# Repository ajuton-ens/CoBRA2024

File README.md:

# CoBRA

Le projet CoBRA (Course de Ballons Réactifs et Autonomes) à pour objectif de construire un ballon dirigeable capable de suivre un parcours de façon autonome et de larguer un colis

## 1 Constitution des équipes

Chaque équipe doit fournir au moins 1 membre à chacun des 4 groupes de travail suivants :
* Préhension & Dépot
* Optimisation de la cinématique de vol
* Modélisation & Contrôle/Commande
* Informatique embarquée & Localisation

## 2 Analyse fonctionnelle et état de l'art
La première séance est consacrée à un travail d'étude générale du problème et d'état de l'art (projet 2023_2024 et autres dirigeables blimp).
* Découper le problème en plusieurs fonctions,
* Pour chaque fonction, spécifier les performances attendues,
* Etudier les solutions retenues en 2023 et les solutions retenues pour d'autres dirigeables,
* Etablir un schéma synoptique du dirigeable.

La semaine suivante, les groupes de travail commenceront leurs études.

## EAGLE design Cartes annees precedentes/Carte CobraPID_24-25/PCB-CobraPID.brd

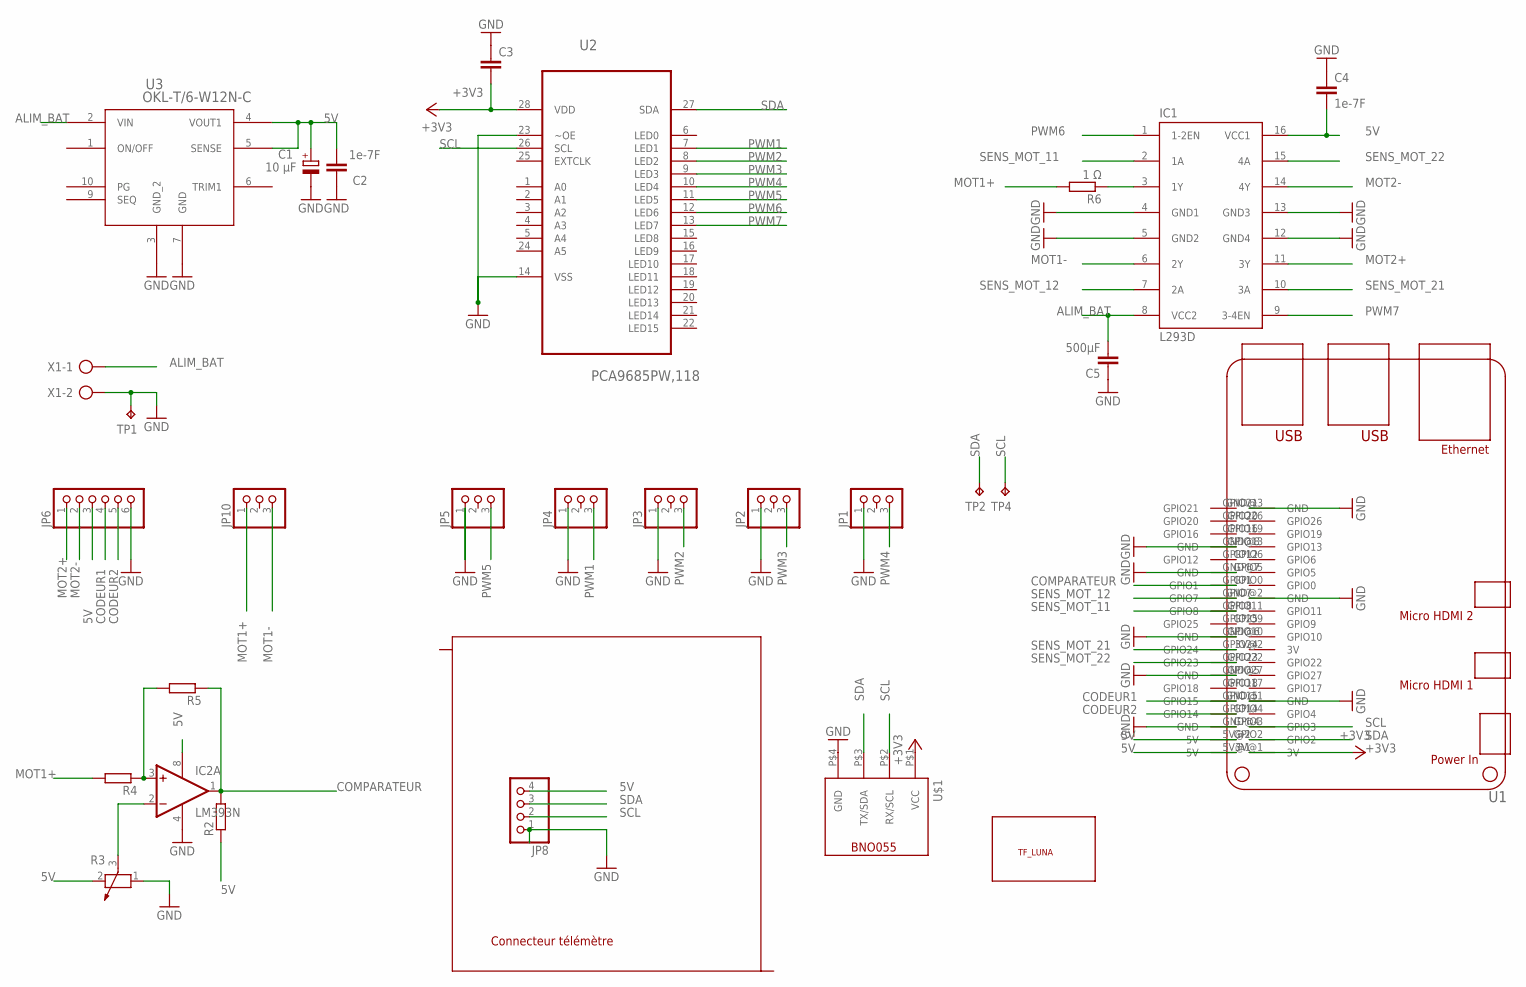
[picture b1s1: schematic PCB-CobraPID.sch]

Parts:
C1: 10 μF; E5-10,5
C2, C4: 1e-7F; C1206
C3: C-EUC1206; C1206
C5: 500μF; C1206
IC1: L293D; DIL16
IC2: LM393N; DIL08
JP1, JP2, JP3, JP4, JP5, JP10: PINHD-1X3/90; 1X03/90
JP6: PINHD-1X6/90; 1X06/90
JP8: PINHD-1X4; 1X04
R2, R4, R5: R-EU_R1206; R1206
R3: POTENTIOMETER_PT-10; PT-10
R6: 1 Ω; R1206
TP1, TP2, TP4: TPPAD1-17; P1-17
U1: RPI5
U2: PCA9685PW,118; SOP65P640X110-28N
U3: OKL-T/6-W12N-C; OKL-T/6-W12N-C_MUR
U$1: MODULE_BNO055
U$2: TF_LUNA
X1: AK500/2

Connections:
5V: C1.+, C2.2, C4.2, IC1.16 (VCC1), IC2.8 (V+), JP6.3, JP8.4, R2.1, R3.2, U1.5V@1 (5V), U1.5V@2 (5V), U3.4 (VOUT1), U3.5 (SENSE)
+3V3: C3.2, U1.3V@1 (3V), U2.28 (VDD), U$1.P$1 (VCC)
ALIM_BAT: C5.2, IC1.8 (VCC2), U3.2 (VIN), X1.1
CODEUR1: JP6.4, U1.GPIO15
CODEUR2: JP6.5, U1.GPIO14
COMPARATEUR: IC2.1 (OUT), R2.2, R5.1, U1.GPIO1
GND: C1.-, C2.1, C3.1, C4.1, C5.1, IC1.4 (GND1), IC1.5 (GND2), IC1.12 (GND4), IC1.13 (GND3), IC2.4 (V-), JP1.1, JP2.1, JP3.1, JP4.1, JP6.6, JP8.1, R3.1, TP1.TP, U1.GND@1 (GND), U1.GND@2 (GND), U1.GND@3 (GND), U1.GND@4 (GND), U1.GND@5 (GND), U1.GND@6 (GND), U1.GND@7 (GND), U1.GND@8 (GND), U2.14 (VSS), U2.23 (~OE), U3.3 (GND_2), U3.7 (GND), U$1.P$4 (GND), X1.2
GND1: JP5.1
MOT1+: JP10.1, R4.2, R6.2
MOT1-: IC1.6 (2Y), JP10.3
MOT2+: IC1.11 (3Y), JP6.1
MOT2-: IC1.14 (4Y), JP6.2
unnamed: IC2.3 (+IN), R4.1, R5.2
unnamed: IC2.2 (-IN), R3.3
unnamed: IC1.3 (1Y), R6.1
PWM1: JP4.3, U2.7 (LED1)
PWM2: JP3.3, U2.8 (LED2)
PWM3: JP2.3, U2.9 (LED3)
PWM4: JP1.3, U2.10 (LED4)
PWM5: JP5.3, U2.11 (LED5)
PWM6: IC1.1 (1-2EN), U2.12 (LED6)
PWM7: IC1.9 (3-4EN), U2.13 (LED7)
SCL: JP8.2, TP4.TP, U1.GPIO3, U2.26 (SCL), U$1.P$2 (RX/SCL)
SDA: JP8.3, TP2.TP, U1.GPIO2, U2.27 (SDA), U$1.P$3 (TX/SDA)
SENS_MOT_11: IC1.2 (1A), U1.GPIO8
SENS_MOT_12: IC1.7 (2A), U1.GPIO7
SENS_MOT_21: IC1.10 (3A), U1.GPIO24
SENS_MOT_22: IC1.15 (4A), U1.GPIO23

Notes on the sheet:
Connecteur télémètre

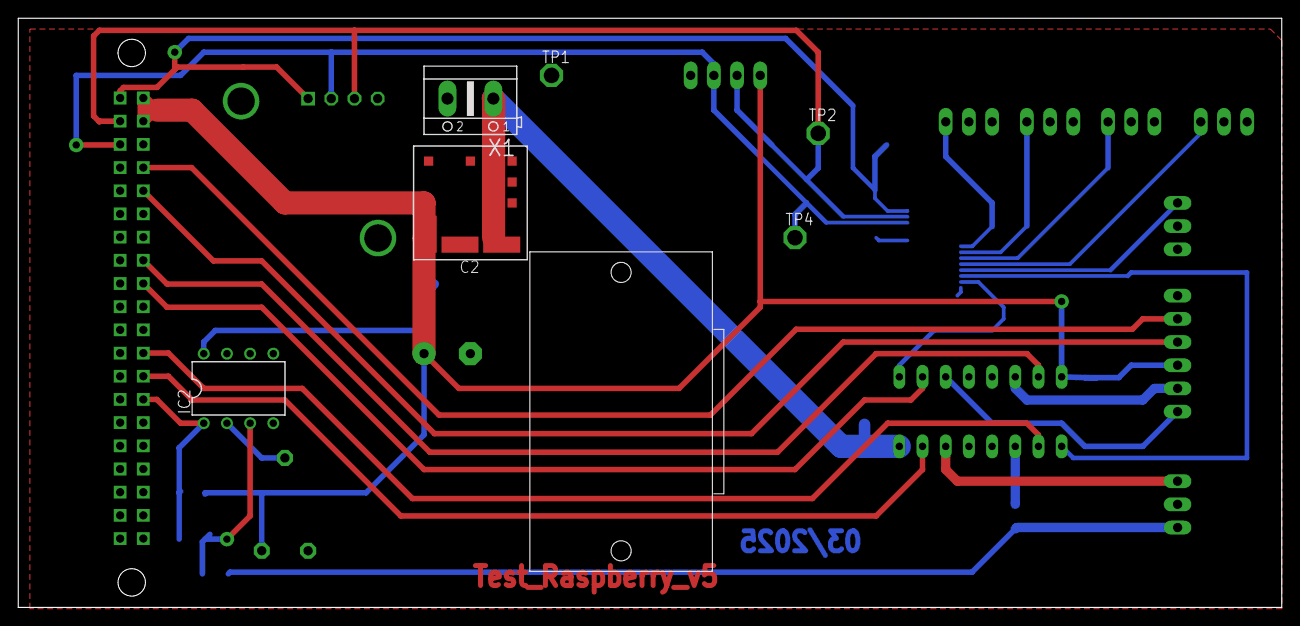
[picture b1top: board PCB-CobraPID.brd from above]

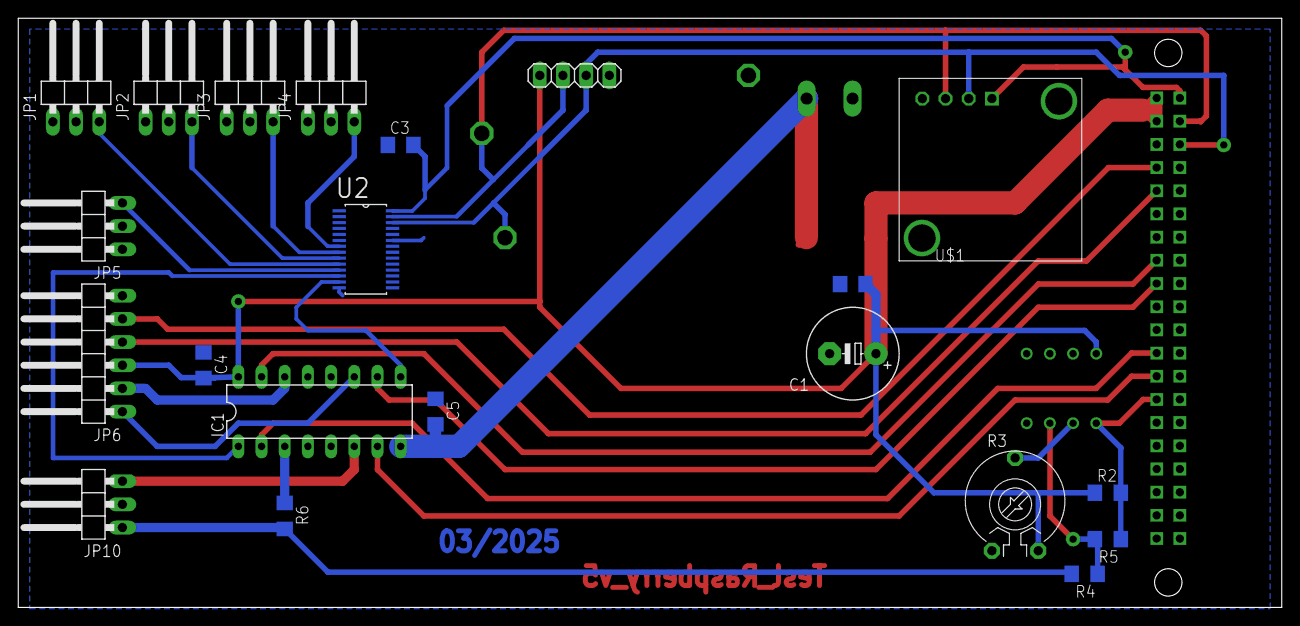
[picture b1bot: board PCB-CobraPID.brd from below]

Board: 2 copper layers, 138.4 x 64.5 mm, 29 parts (21 on the bottom side), 27 nets.

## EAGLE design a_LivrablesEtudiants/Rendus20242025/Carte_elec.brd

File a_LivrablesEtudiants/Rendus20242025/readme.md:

# Info 2024/25

Pour désactiver la sortie 5 volts de la carte Raspberry pi 5

Ouvrir le fichier config.txt: sudo nano /boot/firmware/config.txt

Ajouter la igne suivante :
PSU_MAX_CURRENT=5000

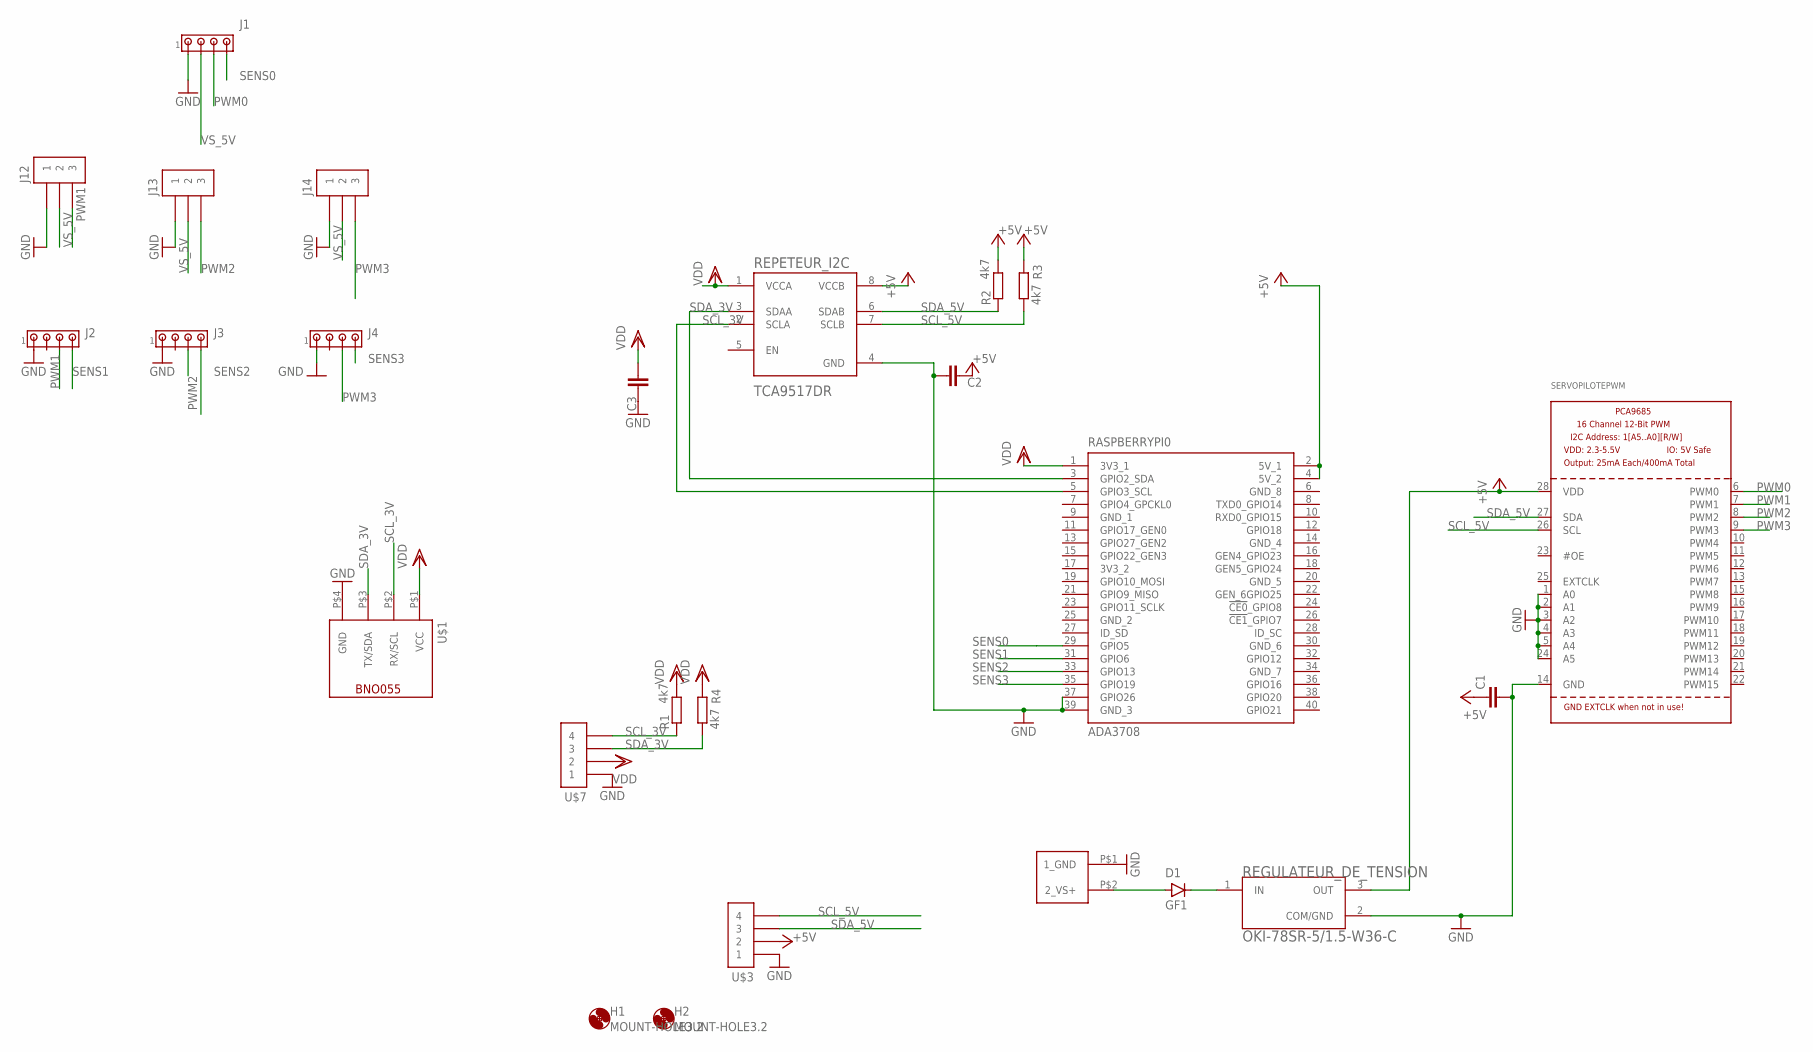
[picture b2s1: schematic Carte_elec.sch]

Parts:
C1, C2, C3: C-EUC1206; C1206
D1: GF1; SMA-DO214AC
H1, H2: MOUNT-HOLE3.2; 3,2
J1, J2, J3, J4: MTA04-100; 10X04MTA
J12, J13, J14: CAVALIER_3
R1, R2, R3, R4: 4k7; R1206
RASPBERRYPI0: ADA3708; MODULE_ADA3708
REGULATEUR_DE_TENSION: OKI-78SR-5/1.5-W36-C; CONV_OKI-78SR-5/1.5-W36-C
REPETEUR_I2C: TCA9517DR; SOIC127P599X175-8N
SERVOPILOTEPWM: PCA9685; TSSOP28
U$1: MODULE_BNO055
U$2: CONN_ALIM
U$3, U$7: MOLEX_4_DROIT

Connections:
3V3_2: RASPBERRYPI0.17 (3V3_2)
+5V: C1.1, C2.1, R2.2, R3.2, RASPBERRYPI0.2 (5V_1), RASPBERRYPI0.4 (5V_2), REGULATEUR_DE_TENSION.3 (OUT), REPETEUR_I2C.8 (VCCB), SERVOPILOTEPWM.28 (VDD), U$3.P$2 (2)
GND: C1.2, C2.2, C3.1, J1.1, J2.1, J3.1, J4.1, J12.P$1 (1), J13.P$1 (1), J14.P$1 (1), RASPBERRYPI0.37 (GPIO26), RASPBERRYPI0.39 (GND_3), REGULATEUR_DE_TENSION.2 (COM/GND), REPETEUR_I2C.4 (GND), SERVOPILOTEPWM.1 (A0), SERVOPILOTEPWM.2 (A1), SERVOPILOTEPWM.3 (A2), SERVOPILOTEPWM.4 (A3), SERVOPILOTEPWM.5 (A4), SERVOPILOTEPWM.14 (GND), SERVOPILOTEPWM.24 (A5), U$1.P$4 (GND), U$2.P$1 (1_GND), U$3.P$1 (1), U$7.P$1 (1)
GND_1: RASPBERRYPI0.9 (GND_1)
GND_2: RASPBERRYPI0.25 (GND_2)
GND_4: RASPBERRYPI0.14 (GND_4)
GND_5: RASPBERRYPI0.20 (GND_5)
GND_6: RASPBERRYPI0.30 (GND_6)
GND_7: RASPBERRYPI0.34 (GND_7)
GND_8: RASPBERRYPI0.6 (GND_8)
unnamed: D1.A, U$2.P$2 (2_VS+)
unnamed: D1.K (C), REGULATEUR_DE_TENSION.1 (IN)
PWM0: J1.3, SERVOPILOTEPWM.6 (PWM0)
PWM1: J2.3, J12.P$3 (3), SERVOPILOTEPWM.7 (PWM1)
PWM2: J3.3, J13.P$3 (3), SERVOPILOTEPWM.8 (PWM2)
PWM3: J4.3, J14.P$3 (3), SERVOPILOTEPWM.9 (PWM3)
SCL_3V: R1.1, RASPBERRYPI0.5 (GPIO3_SCL), REPETEUR_I2C.2 (SCLA), U$1.P$2 (RX/SCL), U$7.P$4 (4)
SCL_5V: R3.1, REPETEUR_I2C.7 (SCLB), SERVOPILOTEPWM.26 (SCL), U$3.P$4 (4)
SDA_3V: R4.1, RASPBERRYPI0.3 (GPIO2_SDA), REPETEUR_I2C.3 (SDAA), U$1.P$3 (TX/SDA), U$7.P$3 (3)
SDA_5V: R2.1, REPETEUR_I2C.6 (SDAB), SERVOPILOTEPWM.27 (SDA), U$3.P$3 (3)
SENS0: J1.4, RASPBERRYPI0.29 (GPIO5)
SENS1: J2.4, RASPBERRYPI0.31 (GPIO6)
SENS2: J3.4, RASPBERRYPI0.33 (GPIO13)
SENS3: J4.4, RASPBERRYPI0.35 (GPIO19)
VDD: C3.2, R1.2, R4.2, RASPBERRYPI0.1 (3V3_1), REPETEUR_I2C.1 (VCCA), U$1.P$1 (VCC), U$7.P$2 (2)
VS_5V: J1.2, J12.P$2 (2), J14.P$2 (2)

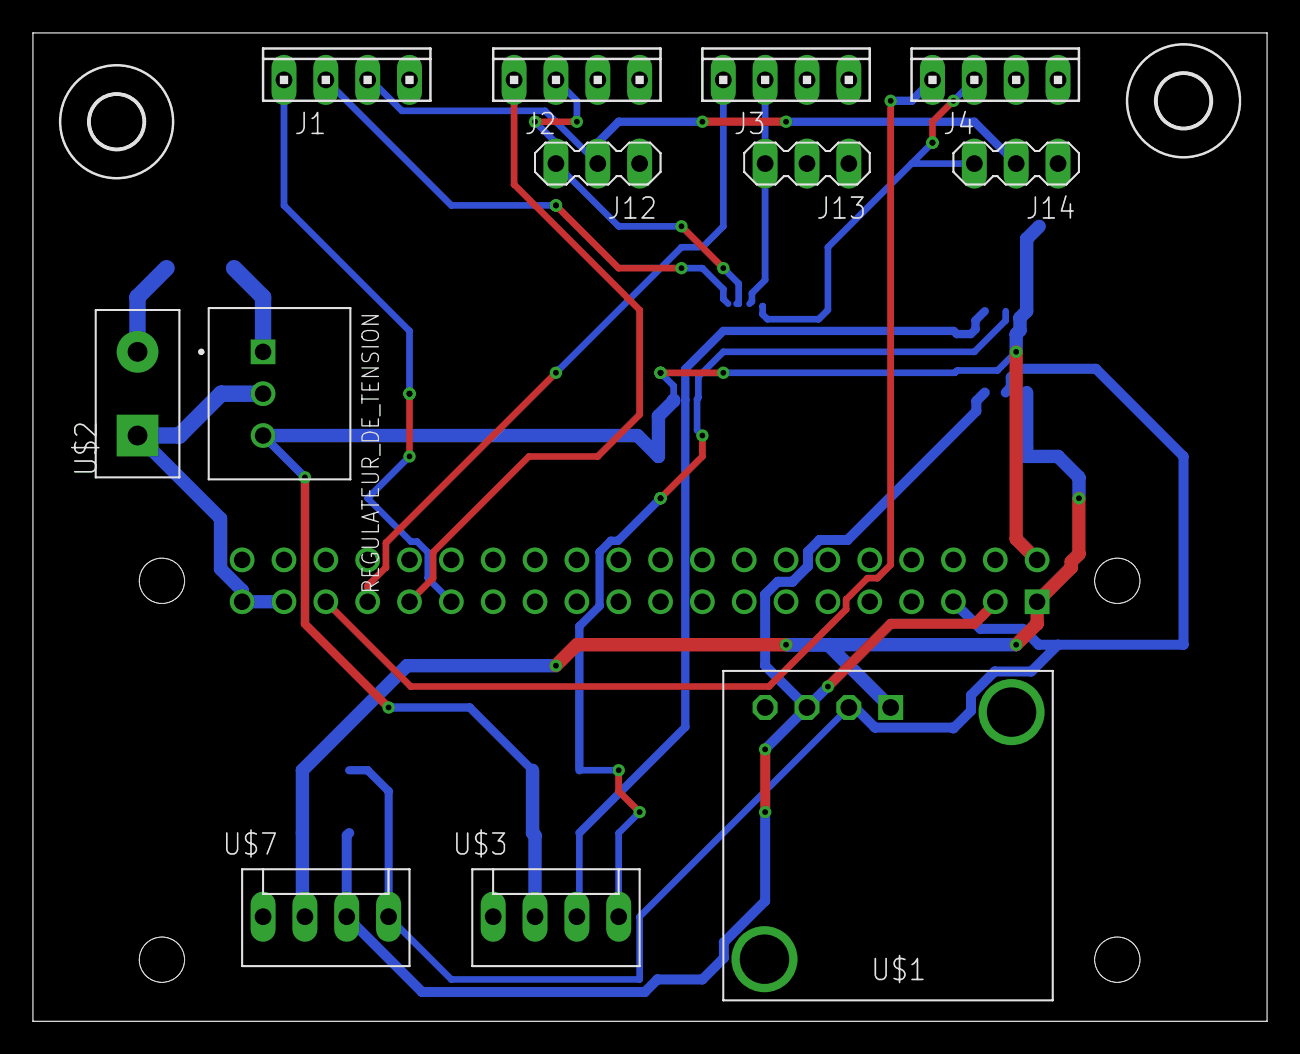
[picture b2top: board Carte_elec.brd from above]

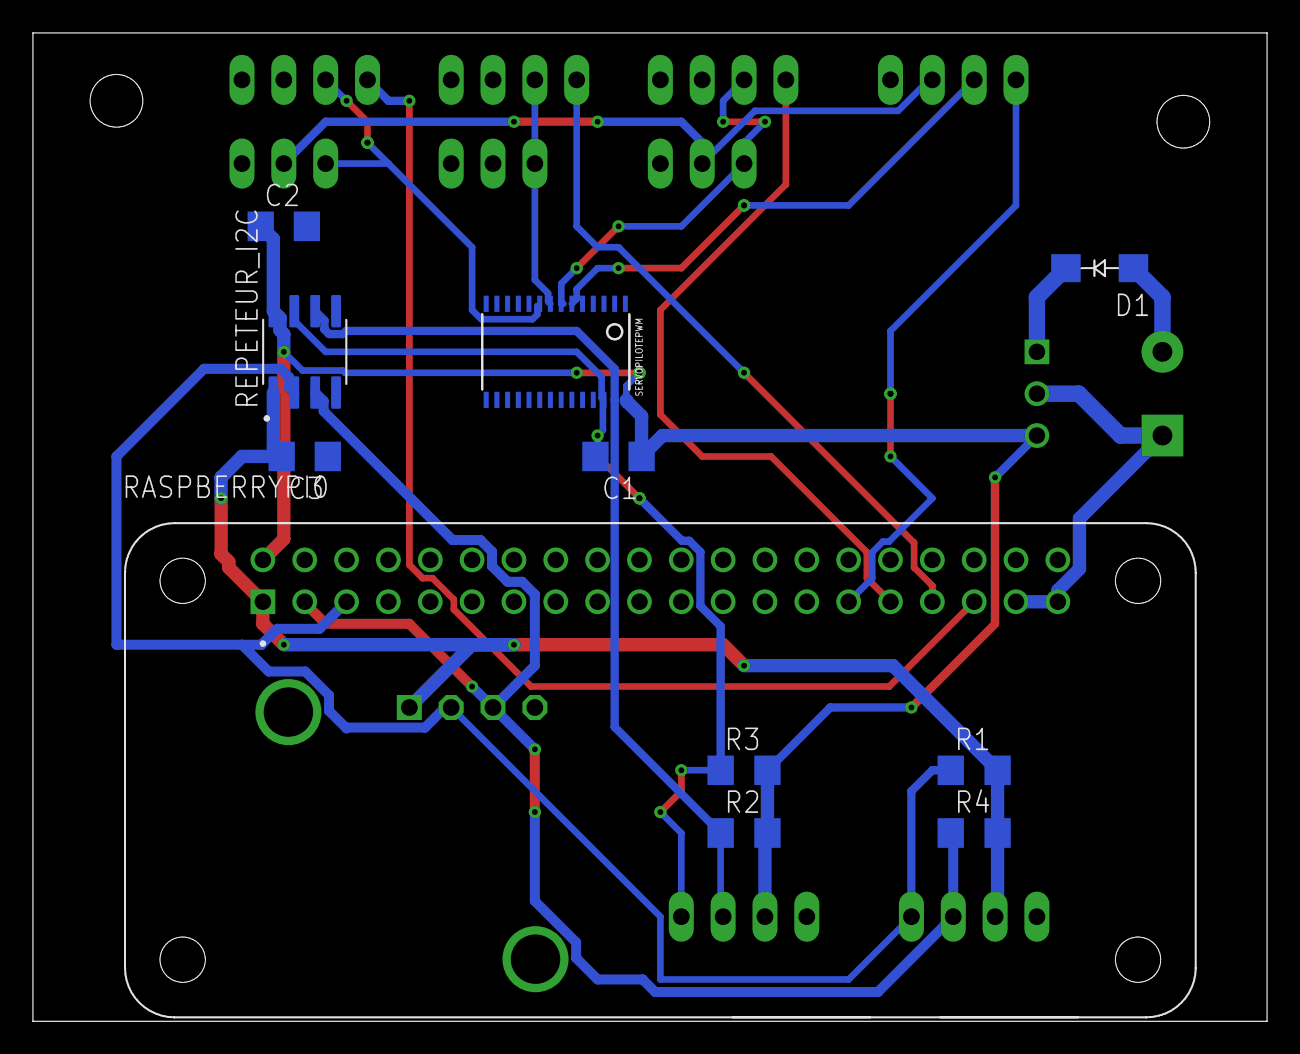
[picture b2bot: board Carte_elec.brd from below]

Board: 2 copper layers, 74.9 x 60.0 mm, 25 parts (11 on the bottom side), 18 nets.

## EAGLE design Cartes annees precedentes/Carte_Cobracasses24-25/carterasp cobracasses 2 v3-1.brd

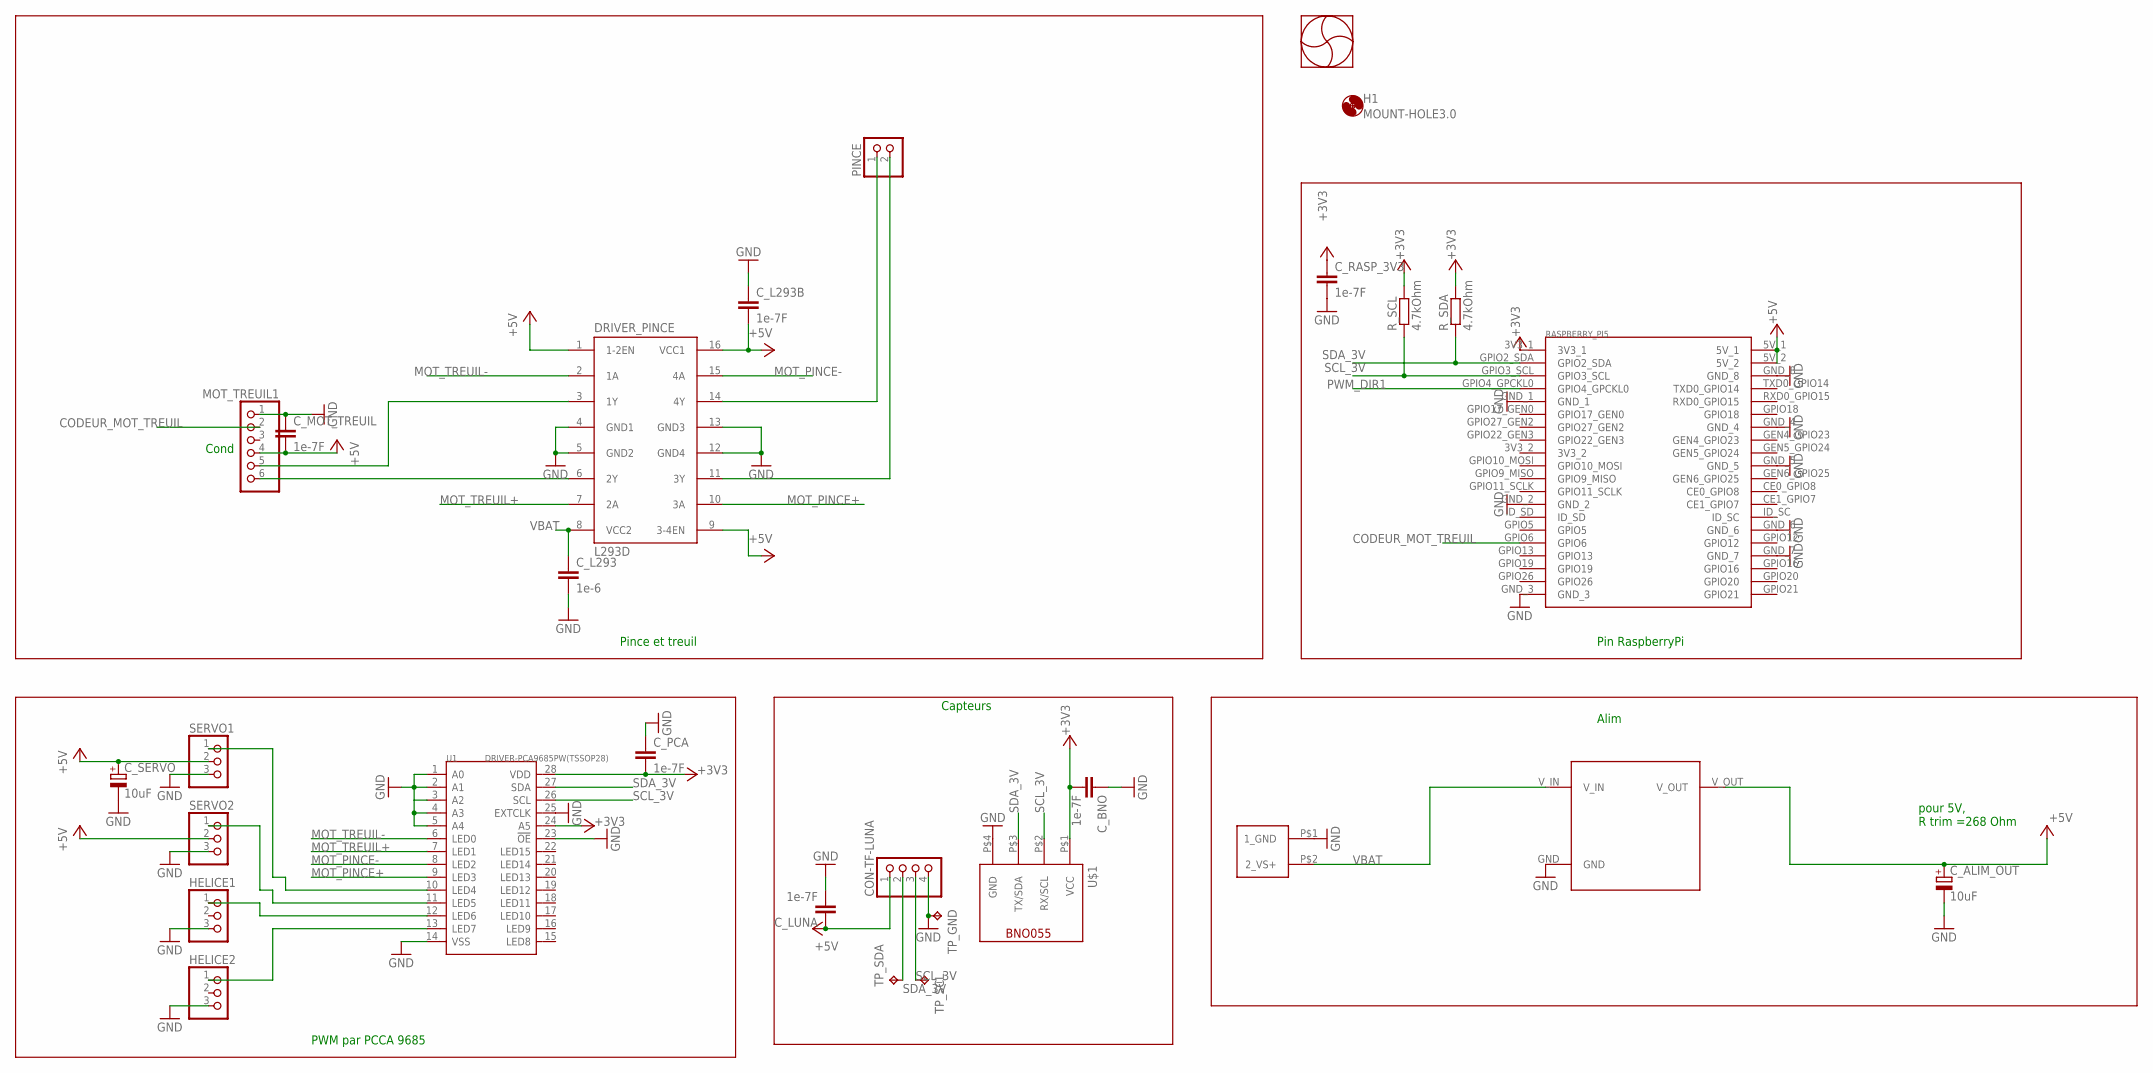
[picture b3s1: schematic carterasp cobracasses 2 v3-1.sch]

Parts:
CON-TF-LUNA: PINHD-1X4; 1X04
C_ALIM_OUT: 10uF; E5-8,5
C_BNO: 1e-7F; C1206
C_L293: 1e-6; C1206
C_L293B: 1e-7F; C1206
C_LUNA: 1e-7F; C1206
C_MOT_TREUIL: 1e-7F; C1206
C_PCA: 1e-7F; C1206
C_RASP_3V3: 1e-7F; C1206
C_SERVO: 10uF; E5-8,5
DRIVER_PINCE: L293D; DIL16
H1: MOUNT-HOLE3.0; 3,0
HELICE1, HELICE2: PINHD-1X3; 1X03
MOT_TREUIL1: PINHD-1X6; 1X06
PINCE: PINHD-1X2; 1X02
R_SCL: 4.7kOhm; R0805
R_SDA: 4.7kOhm; R0805
SERVO1, SERVO2: PINHD-1X3; 1X03
TP_GND: TPPAD1-13; P1-13
TP_SCL: TPPAD1-13; P1-13
TP_SDA: TPPAD1-13; P1-13
U1: DRIVER-PCA9685PW(TSSOP28); TSSOP28-0.65-9.7X4.4MM
U$1: MODULE_BNO055
U$2: CONN_ALIM
U$3: RASPBERRY_PI5; RP5
U$4: OKL_T6_W12
U$5: VENTILLATEUR_RASP

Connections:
+3V3: C_BNO.2, C_PCA.2, C_RASP_3V3.1, R_SCL.2, R_SDA.2, U1.24 (A5), U1.28 (VDD), U$1.P$1 (VCC), U$3.3V3_1
+5V: CON-TF-LUNA.1, C_ALIM_OUT.+, C_L293B.2, C_LUNA.1, C_MOT_TREUIL.2, C_SERVO.+, DRIVER_PINCE.1 (1-2EN), DRIVER_PINCE.9 (3-4EN), DRIVER_PINCE.16 (VCC1), MOT_TREUIL1.4, SERVO1.2, SERVO2.2, U$3.5V_1, U$3.5V_2, U$4.V_OUT
CODEUR_MOT_TREUIL: MOT_TREUIL1.2, U$3.GPIO6
GND: CON-TF-LUNA.4, C_ALIM_OUT.-, C_BNO.1, C_L293.2, C_L293B.1, C_LUNA.2, C_MOT_TREUIL.1, C_PCA.1, C_RASP_3V3.2, C_SERVO.-, DRIVER_PINCE.4 (GND1), DRIVER_PINCE.5 (GND2), DRIVER_PINCE.12 (GND4), DRIVER_PINCE.13 (GND3), HELICE1.3, HELICE2.3, MOT_TREUIL1.1, SERVO1.3, SERVO2.3, TP_GND.TP, U1.1 (A0), U1.2 (A1), U1.3 (A2), U1.4 (A3), U1.5 (A4), U1.14 (VSS), U1.23 (!OE), U1.25 (EXTCLK), U$1.P$4 (GND), U$2.P$1 (1_GND), U$3.GND_1, U$3.GND_2, U$3.GND_3, U$3.GND_4, U$3.GND_5, U$3.GND_6, U$3.GND_7, U$3.GND_8, U$4.GND
MOT_PINCE+: DRIVER_PINCE.10 (3A), U1.9 (LED3)
MOT_PINCE-: DRIVER_PINCE.15 (4A), U1.8 (LED2)
MOT_TREUIL+: DRIVER_PINCE.7 (2A), U1.7 (LED1)
MOT_TREUIL-: DRIVER_PINCE.2 (1A), U1.6 (LED0)
unnamed: DRIVER_PINCE.3 (1Y), MOT_TREUIL1.5
unnamed: DRIVER_PINCE.14 (4Y), PINCE.1
unnamed: SERVO1.1, U1.10 (LED4)
unnamed: SERVO2.1, U1.11 (LED5)
unnamed: HELICE1.1, U1.12 (LED6)
unnamed: HELICE2.1, U1.13 (LED7)
unnamed: DRIVER_PINCE.11 (3Y), PINCE.2
unnamed: DRIVER_PINCE.6 (2Y), MOT_TREUIL1.6
PWM_DIR1: U$3.GPIO4_GPCKL0
SCL_3V: CON-TF-LUNA.3, R_SCL.1, TP_SCL.TP, U1.26 (SCL), U$1.P$2 (RX/SCL), U$3.GPIO3_SCL
SDA_3V: CON-TF-LUNA.2, R_SDA.1, TP_SDA.TP, U1.27 (SDA), U$1.P$3 (TX/SDA), U$3.GPIO2_SDA
VBAT: C_L293.1, DRIVER_PINCE.8 (VCC2), U$2.P$2 (2_VS+), U$4.V_IN

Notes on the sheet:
PWM par PCCA 9685
Pince et treuil
Capteurs
Alim
Cond
Pin RaspberryPi
pour 5V, R trim =268 Ohm

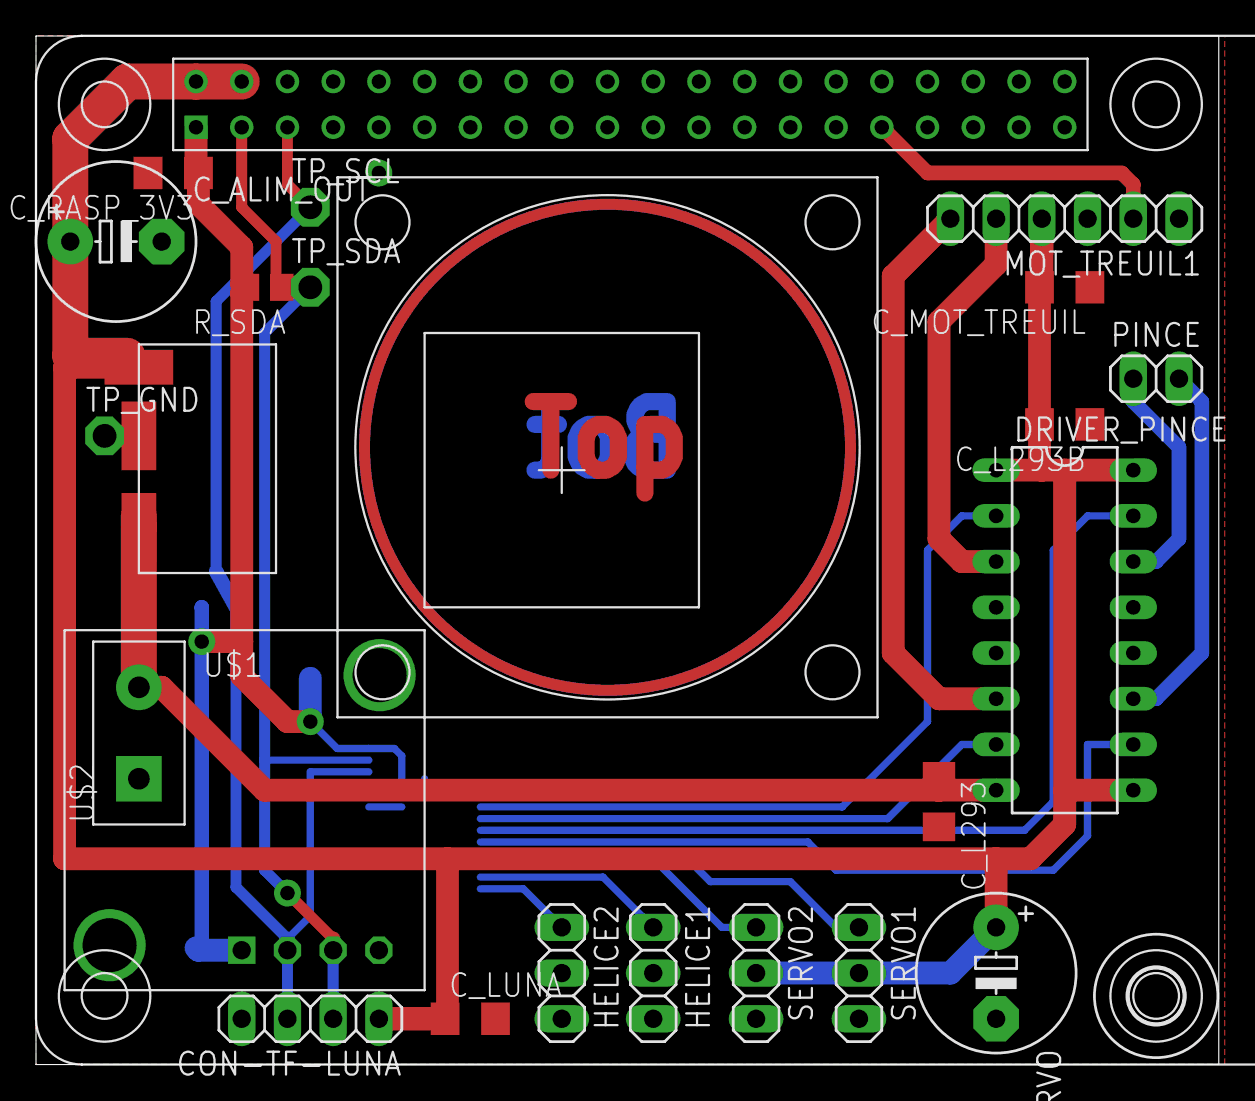
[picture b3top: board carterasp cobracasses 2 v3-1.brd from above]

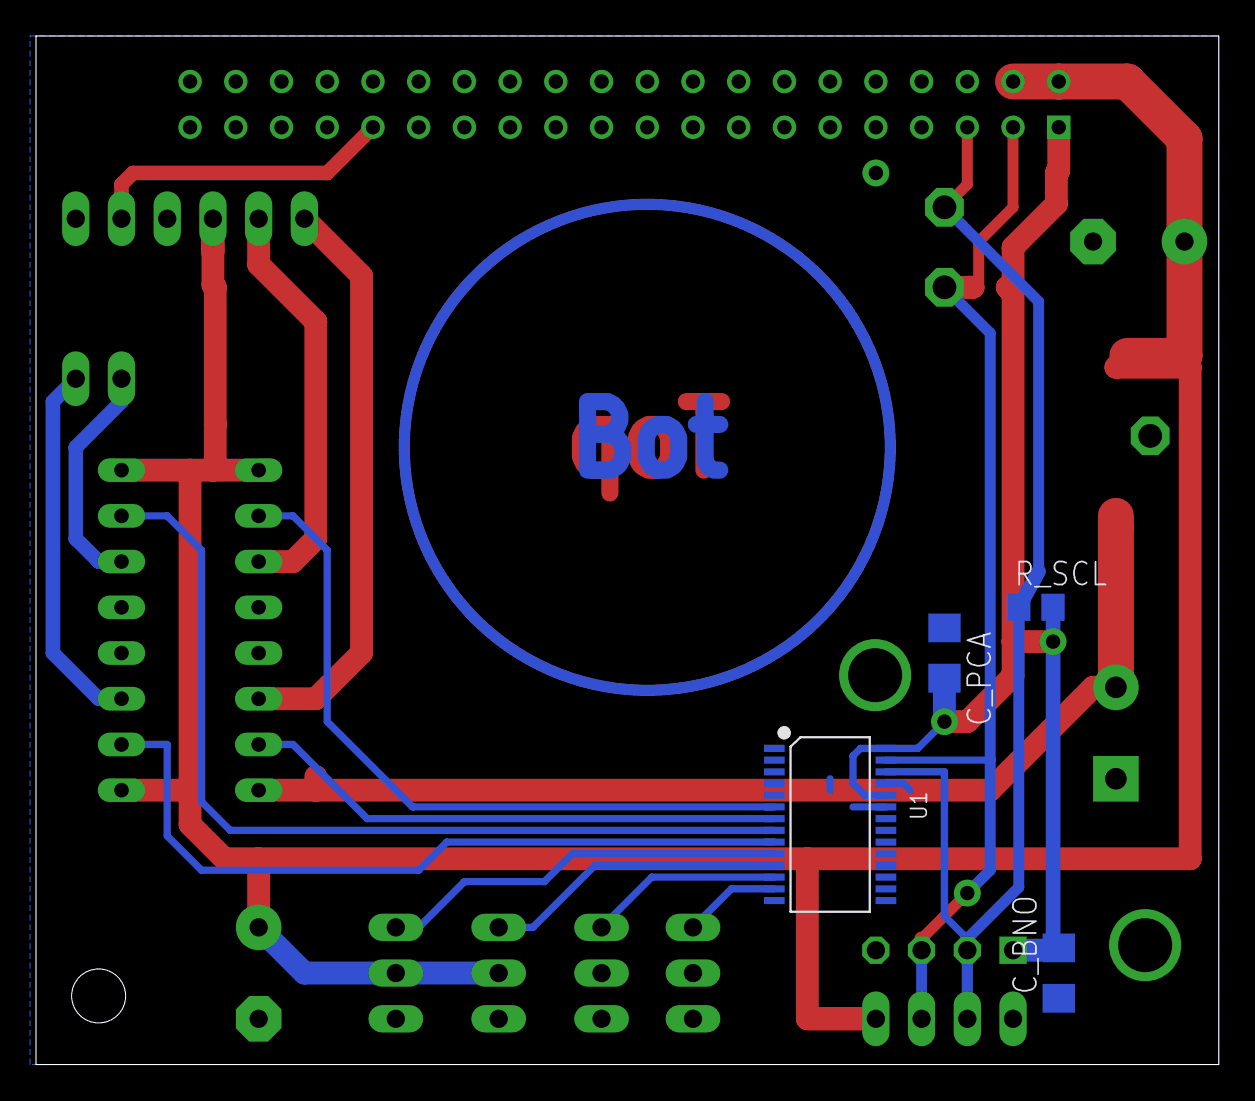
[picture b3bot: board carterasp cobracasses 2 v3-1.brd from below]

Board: 2 copper layers, 65.7 x 57.1 mm, 29 parts (4 on the bottom side), 19 nets.

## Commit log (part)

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2024-10-01 Update 2024
2024-10-03 Mise à jour 2024
2024-10-11 ajout du tutoriel pour la prise en main de la raspberry Pi Zero
2024-10-11 ajout de test_commandes_PS4.py
2024-10-11 Update Caracteristiques_ballon_constructeur.md
    Lien web vers le site, et non vers la vidéo de présentation
2024-10-11 MAJ du guide d'installation de la RPI zero
2024-10-24 Model_Ctrl_Cmd : ajout mesures altitude echelon
    Modelisation ControleCommande : ajout de mesures MatLab de la réponse du dirigeable en altitude à un echelon (consigne de vitesse du moteur de l'hélice située en dessous du dirigeable). Amplitudes 0.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
2024-10-25 Create 2024_2025
2024-10-25 Ajout de l'article apriltag
2024-10-25 Rename Archives2023_2024/cahier_des_charges.docx to cahier_des_charges.docx
2024-10-25 Create fgh
2024-11-15 Code pour la localisation avec les tags
    J'ai déposé le code pour localiser la caméra en utilisant les tags
2024-11-15 Update DetectTagPi5
    Ajout des commentaires
2024-11-15 Update DetectTagPi5
2024-12-06 Add files via upload
    Variateur AM16AT
2024-12-15 Create bibliographie
2024-12-15 Update bibliographie
2025-01-10 Create Presentations_solutions_techniques
2025-01-10 modifications
2025-01-10 présentation demandé par les professeurs
2025-02-05 Deleting DetectTagPi5, necessité de l'adaptation pour deux caméras
2025-02-07 Create CarteElec2024
2025-03-14 Creation du dossier bibliotheques2024_2025
2025-03-28 Version v02 de la commande du generateur PWM
    commande moteurs
2025-03-28 Version v03 de la commande du generateur PWM
    commande moteur brushless. Pas encore implemente MCC
2025-03-28 Version v03 de la mesure du TFLUNA
    capteur telemetre distance TFLUNA
2025-04-11 Versions v04 et v05 de la commande du generateur PWM
2025-04-11 Version v06 de la commande du generateur PWM
2025-05-09 Version v09 de la commande du generateur PWM
2025-05-16 Version v12 de la commande de tous les moteurs
2025-06-07 Ajout des posters
2025-06-10 ajout des rapports
2025-06-10 version de 2025.06.10 du code final
    Dossier 2025.06.10 testé pendant la séance
    Dossier 2025.06.10_chezmoi pas testé, codé après la séance : contient asservissement x,y,z sans asservissement de l'angle heading (c.à.d. l'angle yaw)
2025-06-11 version de 2025.06.11 du code final
    Dossier 2025.06.11 testé pendant la séance
2025-06-12 version de 2025.06.11 du code final (chez moi)
    Dossier 2025.06.11_chezmoi PAS testé
2025-06-12 version de 2025.06.12 du code final (en attendant)
    Dossier 2025.06.12_enattendant PAS testé
2025-06-13 CoBrasCasses : Code entier
2025-10-08 Create READ_ME
2025-10-08 Rename READ_ME to READ_ME.txt
2025-10-08 Rename READ_ME.txt to READ_ME
2025-10-10 Add Tutoriel_Kicad_v1.pdf
2025-10-10 Add LIB_OKL-T_6W12N-C.zip
2025-10-11 Put KiCad Tutoriel in its directory
2025-11-07 clean branch
2025-11-07 add archi.md
2025-11-07 create blank kicad project
2025-11-07 Deleting history
2025-11-07 ajout des docs constructeur du ballon
2025-11-07 rangement...
2025-11-07 Revise objectives and control strategy in readme
    Updated the objectives and control/command sections to include parameter identification and simulation testing.
2025-11-07 Update avancement.md with October progress details
    Added updates on modeling and control progress for October.
2025-11-07 Update avancement.md with progress questions
    Added questions regarding the progress and functionality of programs.
2025-11-07 ajout essais asservissement 202506
2025-11-07 ajout du dossier 20252026
2025-11-07 Revise README for 2025-2026 progress updates
    Updated the README to reflect progress and changes for 2025-2026, including updates on localization solutions and sensor integration.
2025-11-07 datasheets + archi update
2025-11-07 archi capteur pression
2025-11-07 Update avancement.md with November progress notes
    Added notes on progress and issues encountered in November.
2025-11-07 Update avancement.md with november 7th
    Clarified the work on 'lacet' with motor direction details.
2025-11-14 update architecture
2025-11-14 mise à jour archi
2025-11-14 update architecture rp5
2025-11-14 Add mech drawing RPi5
2025-11-14 Update Readme with project advancements
    Added updates on camera testing and GPS Indoor.
2025-11-14 Update Readme with Apriltag spacing analysis
    Added analysis of Apriltag spacing to video stream access notes.
2025-11-19 Ajout de l'article culture sciences de l'ingénieur
2025-11-19 renommage de la partie livrable janvier 2025
2025-11-21 dépot des empreintes
2025-11-21 Update avancement.md with PID settings
    Added PID parameters for control in the document.
2025-11-21 Add BNO055, OKL-T-6 and LPS22HB
2025-11-21 depot empreintes
2025-11-21 Mise à jour symboles et empreintes
2025-11-21 Placement composants
2025-11-21 Add architechture dock
2025-11-21 Début du schéma Kicad
2025-11-21 Add empreinte BNO055_version_pas_en_surface
2025-11-21 Create Vslam
2025-11-28 Add Rapports annes precedentes
2025-11-28 Add empreinte BNO055 pour prototype
2025-11-28 Modif kicad
2025-11-28 Rename Regulateur_tension_bonne_empreinte
2025-11-28 Add telemetre LUNA to architechture_carte_rpi5
2025-11-28 Update motor pin assignments and test library
    Updated motor pin assignments and tested library version.
2025-11-28 Kicad edit
2025-12-01 Ajout des cartes électroniques 2025
2025-12-05 kicad
2025-12-05 Add cartes annees precedentes
2025-12-05 Modify empreinte OKLT6
2025-12-05 Empreinte OKL ok
2025-12-05 Ajoute empreinte xt60
2025-12-05 ajout_empreinte_modele3D
2025-12-05 Add empeintes to carte_rpi5
2025-12-05 Update architechture carte
2025-12-05 pcb_V0.1
2025-12-05 mise à jour PCB
2025-12-10 Ajout d'un article RL/Blimp/Gazebo
2025-12-12 Add pi5-active-cooler.step in Modele 3D
2025-12-12 Add 4628 - porte fusible to empreintes
2025-12-12 Mise à jour du PCB
2025-12-18 Deuxième version du routage pour le PCB
    Il y a encore pas mal d'erreurs au niveau des pads, voir la taille minimale acceptable des pistes pour chaque composant.
2025-12-19 Agrandissement + recablage du PCB
2025-12-23 Mise à jour PCB
    Correction des erreurs sur les pistes / via, ajouts de sérigraphie, logos et vérification du PCB, il reste malgré tout une erreur indiquant que les deux plans de masses de sont pas reliés même avec l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
2025-12-26 Finalisation du PCB
    Toutes les erreurs DRC ont été corrigés. Le PCB est prêt à être tiré.
    Anis.
2026-01-06 Carte modification version finale
2026-01-08 Ajout_schema_carte
2026-01-08 Réorganisation0801
2026-01-08 Modif_schema_synoptique
2026-01-08 fichier_changement_nom
2026-01-09 Ajout Présentation Méca Dirigeable
2026-01-10 Ajout_nw_schema_synoptique
2026-01-30 changement_sens_connecteur_RPI
2026-01-30 modif_plan_masse
2026-02-09 modif PCB 06/02
2026-02-13 modif_PCB_ajout_resistance
2026-02-13 Ajout_fichiers
2026-02-20 Add initial content for CoBRA components documentation
2026-02-20 Add propeller details to composantsCobra.md
    Added propeller information for the CoBRA dirigible.
2026-02-20 Add price for AS2303 F3P motors
2026-02-20 Add link for AS2303 F3P motor
    Added a link for the AS2303 F3P motor specifications.
2026-02-20 Modify propeller details in composantsCobra.md
    Updated the propeller information with a new price and link.
2026-04-03 Ajout_fichier_carte_capteur_pression
2026-04-03 Add carte dock
2026-04-03 add carte
2026-04-03 MAJ_fichier_dock_helium
2026-04-03 MAJ_carte_dock_helium
2026-04-03 ajout_librairie_ESP328devboard
2026-04-10 Creation_fichier_carte_dock_elec
2026-04-10 Codes_capteur_pression_et_ESP32
2026-04-10 Schema_de_cablage_ESP32_LPS22
2026-04-10 Modif_carte_elec
2026-04-17 h
    h
2026-04-17 Modif_schema_creationPCB
2026-04-17 Update composantsCobra.md with new components
    Added ESC, LiDAR, accelerometer, and pressure sensor details.
2026-04-17 carte_dock
2026-04-17 ajout_carte_rpi5
2026-04-17 carte_dock_helium
2026-05-22 mise à jour
2026-05-22 Create Programmes_Eloi
2026-05-22 Create test
2026-05-22 Update BLE Program
2026-05-22 MAJ DOCK ELEC
2026-05-22 Rename libraires_externes.txt to .info_libraires_externes.txt
2026-05-22 Rename asserv_h_2025.py to main.py
2026-05-22 Update BLE Arduino and Python Programs
2026-05-22 maj carte
2026-05-23 modif carte_dirigeable
2026-05-23 modif2_carte_dirigeable
2026-05-29 modif PCB_carte_doc
2026-05-29 Update codes Capteur Pression
2026-05-29 modif1
2026-06-04 Modif_carte_dock
2026-06-04 rapport
2026-06-07 modif_carte_dick
2026-06-15 Add readme for camera calibration automation
    Added information about automated camera calibration process.
2026-06-15 Rename readme2 to readme2.md
2026-06-15 Update readme2.md for camera calibration details
    Clarified the process of camera calibration and photo capture.
2026-06-15 Create readme2.md with usage instructions
    Added usage instructions for Adam_2026 codes and related scripts.

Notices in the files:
parts and their libraries:
COPYRIGHT: Copyright (C) 2025 Ultra Librarian. All rights reserved.
